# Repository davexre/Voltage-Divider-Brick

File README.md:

# Voltage Divider Brick

This is a small board that implements a [voltage divider](https://en.wikipedia.org/wiki/Voltage_divider), making it easy to keep high voltages off a processor board,
like an Arduino. It's inspired by ElecFreaks Octopus bricks. They used to make a voltage divider brick much like this
one - in fact, I own one and am using it with my [Induction Annealer](https://github.com/davexre/Annealer-v3-PCB) project. 
In trying to help some other folks set their annealers up for Arduino control, I noticed that Octopus' bricks are no longer
available, and there's not a brick-like board out there that easily fills the gap. So, I put this one together.

The design changes are really that I chose to use axial resistors (to make assembly and repair easier), and I changed the
input connector to a 5mm pitch version that allows wire sizes up to 12AWG. 

### Pictures!

- [Front of board](images/VoltageDividerv1Front.png)
- [Back of board](images/VoltaqeDividerv1Back.png)

### Bill of Materials

- 1x [CUI Devices TB001-500-02BE](https://www.mouser.com/ProductDetail/CUI-Devices/TB001-500-02BE?qs=vLWxofP3U2zBBnHgU5u3DA%3D%3D)
- 1x [Molex 22-23-2021](https://www.mouser.com/ProductDetail/molex/22-23-2021/?qs=ILqg114nvd4YKlRlbo3yMg%3D%3D&countrycode=US&currencycode=USD)
- 2 appropriate resistors

### Resistor choices

You can choose whatever resistors make sense to you. Normally, for best results, precision resistors would be recommended for
this role. The original Octopus board divided the input voltage by 16, so R1 was 15kOhm, and R2 was 1kOhm. Mouser has equivalent
axial resistors available for both:

- [1 kOhm - .1% 15PPM 1/4W](https://www.mouser.com/ProductDetail/TE-Connectivity-Neohm/YR1B1K0CC?qs=sGAEpiMZZMtlubZbdhIBIIvX6HIFvcbFzVJZ4ENBTC8%3D)
- [15 kOhm - .1% 15PPM 1/4/W](https://www.mouser.com/ProductDetail/TE-Connectivity-Neohm/YR1B15KCC?qs=VHcS2MTj4gZfAJSm%2FAKdUg%3D%3D)

### Connectors

J1 can really be any .1" pitch connector you wish to use. The Molex connector indicated includes polarity and a locking
feature, but you could solder directly to it, or use normal breakaway header pins, or anything else you like.

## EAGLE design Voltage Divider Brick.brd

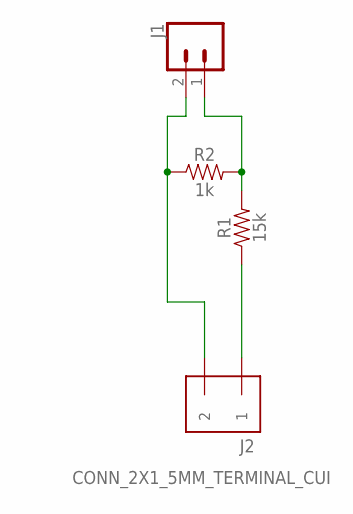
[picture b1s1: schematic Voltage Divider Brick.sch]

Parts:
J1: CONN_02POLAR_LOCK; MOLEX-1X2_LOCK
J2: CONN_2X1_5MM_TERMINAL_CUI; CONN_2X1_5MM_TERMINAL_CUI_HOLE
R1: 15k; AXIAL-0.3
R2: 1k; AXIAL-0.3

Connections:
unnamed: J1.1, R1.P$2 (2), R2.P$2 (2)
unnamed: J2.P$1 (1), R1.P$1 (1)
unnamed: J1.2, J2.P$2 (2), R2.P$1 (1)

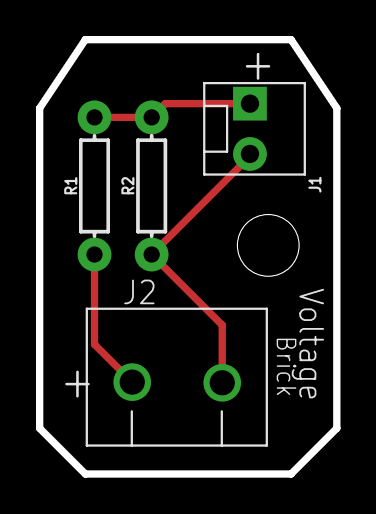
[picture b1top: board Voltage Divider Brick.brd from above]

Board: 2 copper layers, 16.5 x 24.1 mm, 4 parts (0 on the bottom side), 3 nets.

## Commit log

2020-05-18 Initial version
    First version of voltage divider brick board design and schematic.
2020-05-18 Initial README
2020-05-18 Typo fix
2020-05-18 Added board images
2020-05-18 Added images
2020-05-26 Project description
2020-05-31 Improved labeling

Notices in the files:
parts and their libraries:
SparkFun-Connectors: Licensing: Creative Commons ShareAlike 4.0 International - https://creativecommons.org/licenses/by-sa/4.0
